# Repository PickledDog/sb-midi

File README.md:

# sb-midi
 "Sound Blaster MIDI" cable, board fits in the connector shell

Shown here installed in the connector shell from a cheap eBay MIDI cable

## Overview
This little board provides a way to build an active MIDI Out cable that plugs into the gameport of a vintage PC sound card (or [HardMPU-WT](https://github.com/PickledDog/hardmpu-wt)). It does not provide MIDI In. With this board and BOM, you will be able to make a proper buffered MIDI cable that can be used with any gameport sound card.

## Assembly
When ordering boards, select 1.2mm-thick PCB. You can use regular 1.6mm (as in my build), but it's an *extremely* tight fit - not recommended.

Sandwich the board between the two rows of solder cups on the D-sub connector, and solder all 15 cups down on both sides. With the board secured to the connector, go ahead and solder down all the SMT parts.

Solder the cable to the 3 necessary MIDI pins (2, 4, and 5) in the DIN plug. Connect the cable screen (if present) to pin 2. Solder the wires at the other end to the numbered pads on the board. Fasten the cable clamp (included with the D-sub backshell) around the cable so that there's a little slack on the wires when everything's inside the backshell. Assemble the backshell with everything inside, and you're good to go.

### But I can't solder SMT!
Wanna learn? This is a pretty good place to start - most parts are simple 2-terminal ones, and the most complex parts are the 3-terminal transistors. All passives are friendly 0805 parts, and the board's pads are enlarged for hand-soldering. Get some [tweezers](https://www.ebay.com/sch/i.html?_nkw=smt+tweezers) and follow a guide online - 2 and 3 terminal parts are easy!

### I wanna connect a joystick as well!
You'll need a DA-15 female socket and some 10-core cable to wire it in. Solder the necessary wires to the solder cups, and route the wires over the top and bottom of the board. Note that you cannot connect a joystick to a HardMPU-WT; it's MIDI-only.

## Part selection
This project is basically all jellybean parts - just use what you have on hand as applicable. R1 and R4 don't have to be *exactly* 240Ω, so long as they both add up to around ~480Ω (for example, you can use a 200Ω and a 270Ω if you want, or just two 220Ω). You'll need to get some cable - the MIDI Manufacturer's Association recommends shielded twisted pair (shield + one pair), an example of which is listed below. Another option is to cut an existing MIDI cable in half (make two cables!)

## Parts list
Bill Of Materials and part references are below. The specified parts are just the ones I used, and can be substituted as needed - Mouser links provided for convenience and reference. The listed cable is purchased by the foot.

| Reference | Value | Qty | Mouser link |
| --------- | ----- | --- | ----------- |
| C1, C2 | 2.2nF ceramic | 2 | [KEMET C0805C222K5RACTU](https://www.mouser.com/ProductDetail/80-C0805C222K5R) |
| J1 | D-Sub DA-15 male | 1 | [Amphenol L717SDA15P](https://www.mouser.com/ProductDetail/523-L717SDA15P) |
| | backshell | 1 | [Kobiconn 156-2015-EX](https://www.mouser.com/ProductDetail/156-2015-EX) |
| Q1, Q2 | MMBT3904 | 2 | [Diodes MMBT3904-7-F](https://www.mouser.com/ProductDetail/621-MMBT3904-F) |
| R1, R4 | 240Ω resistor | 2 | [Yageo RC0805FR-07240RL](https://www.mouser.com/ProductDetail/603-RC0805FR-07240RL) |
| R2 | 10kΩ resistor | 1 | [Yageo RC0805FR-0710KL](https://www.mouser.com/ProductDetail/603-RC0805FR-0710KL) |
| R3 | 2k2Ω resistor | 1 | [Yageo RC0805FR-072K2L](https://www.mouser.com/ProductDetail/603-RC0805FR-072K2L) |
| | 5-pin DIN plug | 1 | [CUI SD-50](https://www.mouser.com/ProductDetail/490-SD-50) |
| | 1P STP cable | | [AlphaWire M9520010](https://www.mouser.com/ProductDetail/602-M9520010BK199) |

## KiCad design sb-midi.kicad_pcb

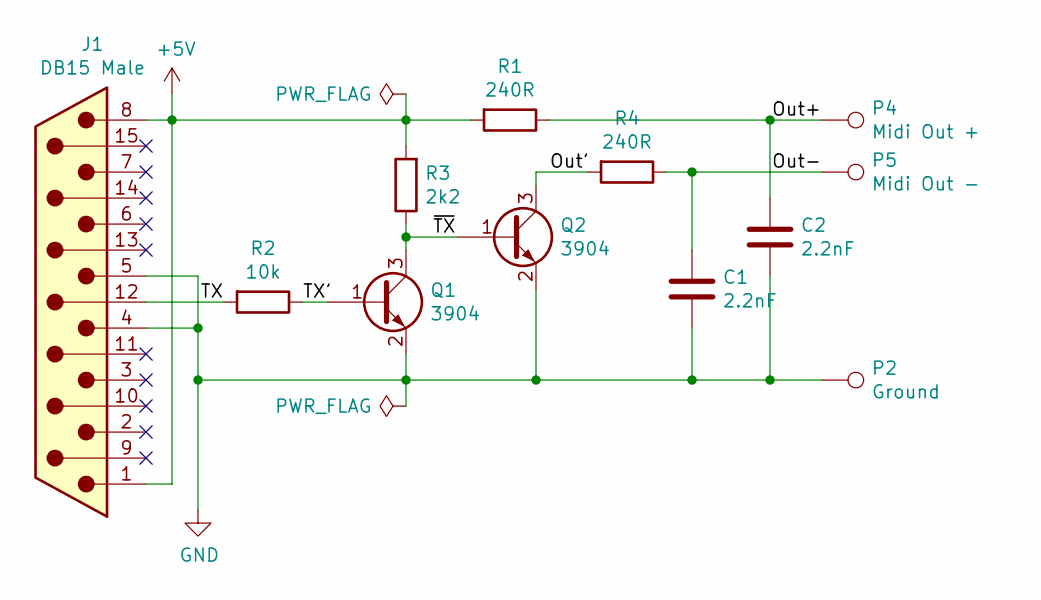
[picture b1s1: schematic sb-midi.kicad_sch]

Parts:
C1, C2: 2.2nF; C_0805_2012Metric_Pad1.18x1.45mm_HandSolder
J1: DB15 Male; DSUB-15_Male_EdgeMount_P2.77mm
P2: Ground; TestPoint_Pad_2.0x2.0mm
P4: Midi Out +; TestPoint_Pad_2.0x2.0mm
P5: Midi Out -; TestPoint_Pad_2.0x2.0mm
Q1, Q2: 3904; SOT-23
R1, R4: 240R; R_0805_2012Metric_Pad1.20x1.40mm_HandSolder
R2: 10k; R_0805_2012Metric_Pad1.20x1.40mm_HandSolder
R3: 2k2; R_0805_2012Metric_Pad1.20x1.40mm_HandSolder

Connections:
+5V: J1.1, J1.8, R1.2, R3.2
/Out': Q2.3 (C), R4.2
/Out+: C2.1, P4.1, R1.1
/Out-: C1.1, P5.1, R4.1
/TX: J1.12, R2.2
/TX': Q1.1 (B), R2.1
/~TX: Q1.3 (C), Q2.1 (B), R3.1
GND: C1.2, C2.2, J1.4, J1.5, P2.1, Q1.2 (E), Q2.2 (E)

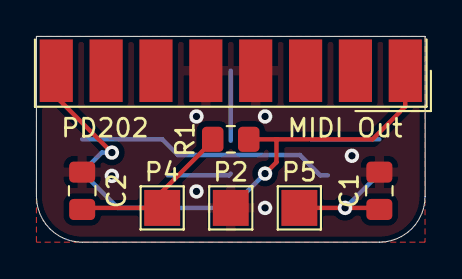
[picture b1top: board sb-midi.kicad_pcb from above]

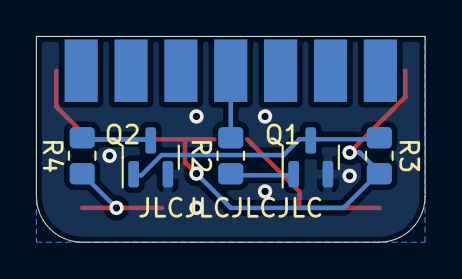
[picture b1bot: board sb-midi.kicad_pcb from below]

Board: 2 copper layers, 21.6 x 11.4 mm, 12 parts (5 on the bottom side), 8 nets.

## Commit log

2023-07-07 Add README file
2023-07-16 Update info about cable details
2023-10-01 Add choice of cable
